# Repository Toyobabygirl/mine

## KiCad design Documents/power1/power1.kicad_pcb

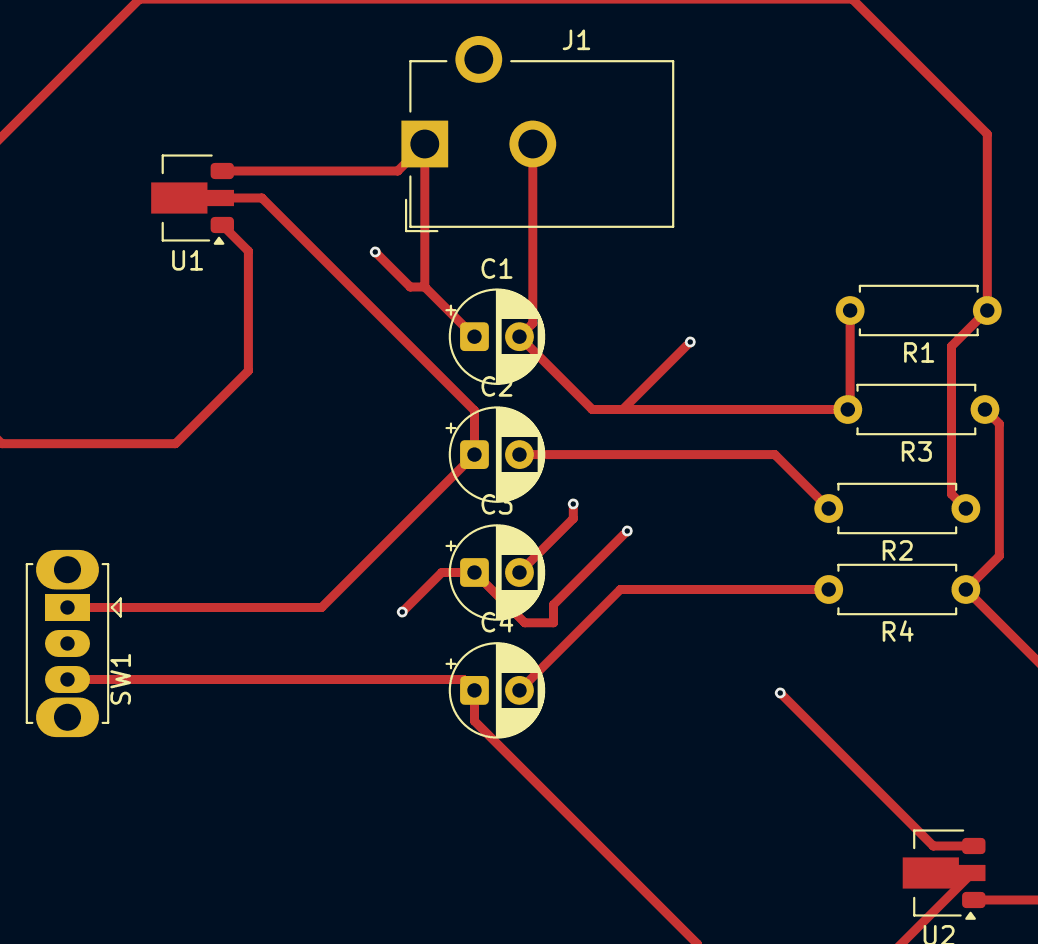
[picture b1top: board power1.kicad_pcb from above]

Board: 2 copper layers, 12 parts (0 on the bottom side), 8 nets.

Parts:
C1, C2, C3, C4: C; CP_Radial_D5.0mm_P2.50mm
J1: Jack-DC; BarrelJack_CUI_PJ-102AH_Horizontal
R1, R3: 720; R_Axial_DIN0207_L6.3mm_D2.5mm_P7.62mm_Horizontal
R2, R4: 240; R_Axial_DIN0207_L6.3mm_D2.5mm_P7.62mm_Horizontal
SW1: SW_DPST_x2; SW_Slide_SPDT_Straight_CK_OS102011MS2Q
U1, U2: LM317L_SOT-89; SOT-89-3

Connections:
GND: C1.2, C3.2, J1.2, R1.2, R3.2
unnamed: C2.2, R2.2
unnamed: C4.2, R4.2
unnamed: C2.1, SW1.1 (A), U1.2 (VO)
unnamed: C4.1, SW1.3 (A), U2.2 (VO)
unnamed: R1.1, R2.1, U1.1 (ADJ)
unnamed: C1.1, C3.1, J1.1, U1.3 (VI), U2.3 (VI)
unnamed: R3.1, R4.1, U2.1 (ADJ)

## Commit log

2025-09-24 mine
2026-04-16 included all the power file
2026-06-02 The virtual hard drive
2026-06-02 The virtual hard drive edited
2026-06-02 made some changes in the code due to the review given
